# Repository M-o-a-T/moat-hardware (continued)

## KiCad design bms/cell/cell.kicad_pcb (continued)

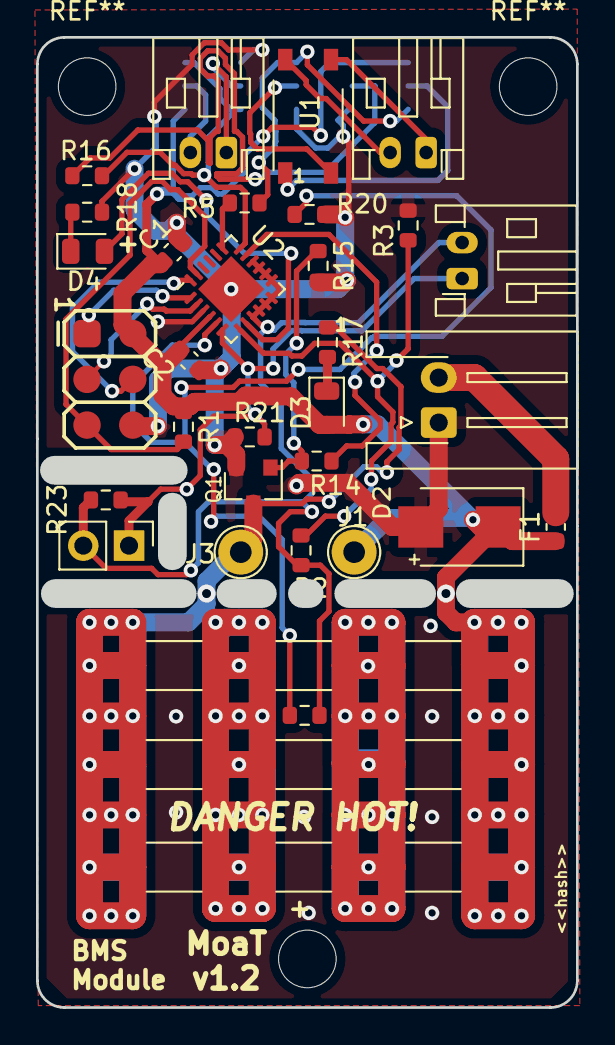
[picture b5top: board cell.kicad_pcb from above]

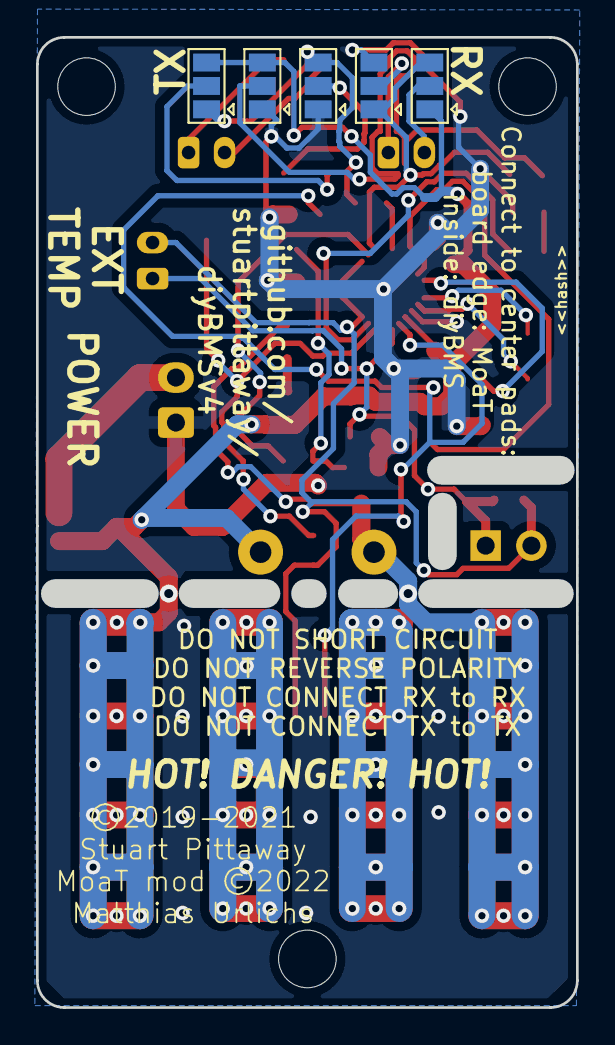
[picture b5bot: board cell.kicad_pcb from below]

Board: 2 copper layers, 30.0 x 53.9 mm, 44 parts (5 on the bottom side), 29 nets.

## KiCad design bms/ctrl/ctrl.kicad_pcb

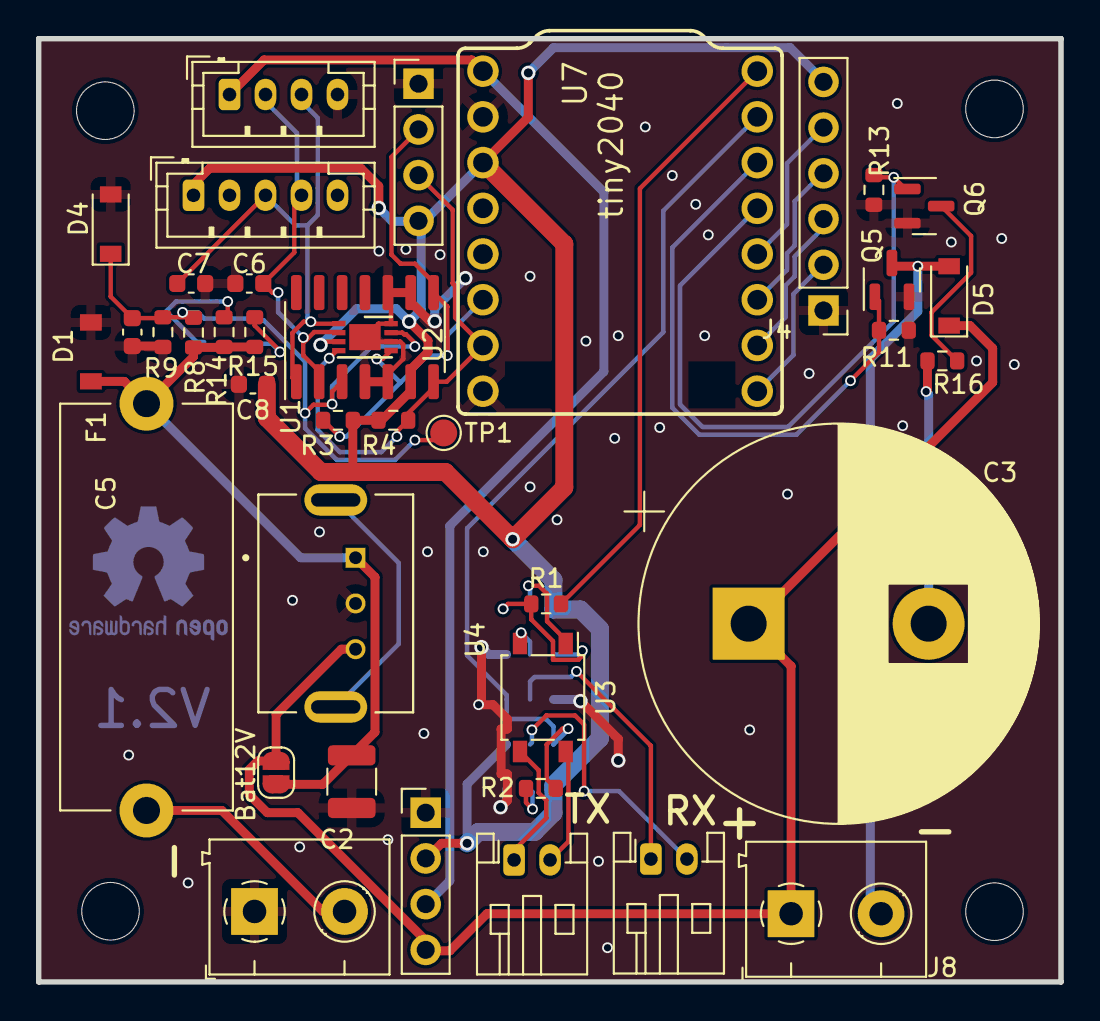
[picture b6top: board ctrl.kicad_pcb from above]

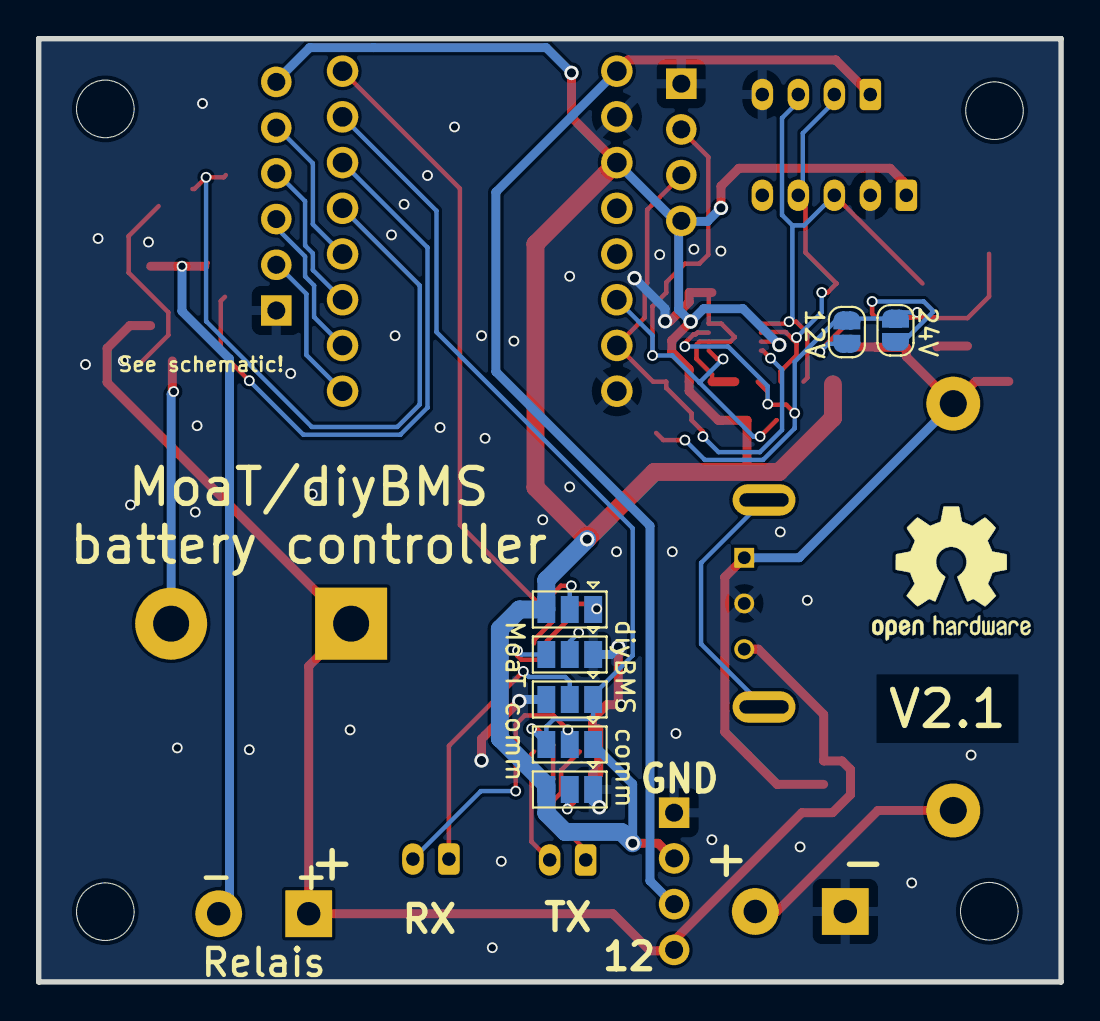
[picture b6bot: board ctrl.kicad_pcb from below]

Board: 2 copper layers, 56.8 x 52.4 mm, 46 parts (7 on the bottom side), 33 nets.

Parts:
C2: CP_1µ_100V_0805; R_1210_3225Metric
C3: CP_22m_16V; CP_Radial_D22.0mm_P10.00mm_SnapIn
C5, C6, C7, C8: CP_100n_50V_0603; C_0603_1608Metric
D1: D_TVS_70V; SOD-123FL
D4: D_Zener_3V3; D_SOD-123
D5: 1N4148; D_SOD-123
F1: Fuse; Fuseholder_Cylinder-5x20mm_Stelvio-Kontek_PTF78_Horizontal_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
J1, J8: Conn_01x02_Female; Conn_P5.0mm_2_Lumberg
J4: Conn_01x06; PinHeader_1x06_P2.54mm_Vertical
J5, J12: Conn_01x04; PinHeader_1x04_P2.54mm_Vertical
J6: Conn_LEM_5; JST_PH_B4B-PH-K_1x04_P2.00mm_Vertical
J10: Conn_LEM_3; JST_PH_B5B-PH-K_1x05_P2.00mm_Vertical
JP1, JP2, JP3, JP4, JP5: SolderJumper_3_Bridged12; SolderJumper-3_P1.3mm_Open_Pad1.0x1.5mm
JP11: Bat12V; SolderJumper-2_P1.3mm_Open_RoundedPad1.0x1.5mm
JP12: 24V; SolderJumper-2_P1.3mm_Open_RoundedPad1.0x1.5mm
JP13: 12V; SolderJumper-2_P1.3mm_Open_RoundedPad1.0x1.5mm
Q5, Q6: DMN2058U-7; SOT-23
R1: R_220_0603; R_0603_1608Metric
R2: R_2k2_0603; R_0603_1608Metric
R3, R4: R_5k1_0603; R_0603_1608Metric
R8, R14, R15: R_750k_0603; R_0603_1608Metric
R9: R_36k_0603_1; R_0603_1608Metric
R11, R13: R_1M_0603; R_0603_1608Metric
R16: R_22_0603; R_0603_1608Metric
RX1: Conn_01x02_Male; JST_PH_S2B-PH-K_1x02_P2.00mm_Horizontal
TP1: TestPoint; TestPoint_Pad_D1.5mm
TX1: Conn_01x02_Male; JST_PH_S2B-PH-K_1x02_P2.00mm_Horizontal
U1: MCP3428; SOIC-14_3.9x8.7mm_P1.27mm
U2: MCP3426-xMC; DFN-8-1EP_3x2mm_P0.5mm_EP1.75x1.45mm
U3: VOS618A; SO-4_4.4x4.3mm_P2.54mm
U4: TSR_1-48150WI
U7: tiny2040

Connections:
+3V3: C8.1, J4.6, J5.4, J10.1 (+), J12.2, JP1.3 (B), JP3.1 (A), JP5.3 (B), R3.1, R4.1, U1.6 (VDD), U2.3 (VDD), U7.3 (3V3)
+5V: J6.1 (+), J12.3, U7.1 (VBUS)
+12V: C3.1, D5.1 (K), J8.1, J12.4, JP11.2 (B), U4.3 (+VOUT)
ADC_BAT_I: C7.1, J6.3 (Out), J10.3 (Out), U1.1 (CH1+), U2.1 (CH1+)
ADC_BAT_U: C5.1, D4.1 (K), JP12.2 (B), JP13.2 (B), R8.2, R9.1, TP1.1, U1.3 (CH2+), U2.7 (CH2+)
ADC_REF_I: C6.1, J6.2 (Ref), J10.4 (Ref), U1.2 (CH1-), U2.2 (CH1-)
GND: C2.2, C5.2, C6.2, C7.2, C8.2, D1.2 (A), D4.2 (A), J1.1, J4.1, J5.1, J6.4 (GND), J10.2 (GND), J12.1, JP2.1 (A), JP4.3 (B), JP5.1 (A), Q5.2 (S), Q6.2 (S), R9.2, R11.2, R13.2, U1.4 (CH2-), U1.5 (VSS), U1.9 (Adr0), U1.10 (Adr1), U2.6 (VSS), U2.8 (CH2-), U2.9 (VSS), U4.2 (GND), U7.2 (GND), U7.8 (GND)
I2C0_SCL: J5.2, R3.2, U1.8 (SCL), U2.5 (SCL), U7.6 (GP27)
I2C0_SDA: J5.3, R4.2, U1.7 (SDA), U2.4 (SDA), U7.7 (GP26)
IO1: J4.5, U7.12 (GP4)
IO2: J4.4, U7.11 (GP5)
IO3: J4.3, U7.10 (GP6)
IO4: J4.2, U7.9 (GP7)
unnamed: C3.2, R16.2
unnamed: D5.2 (A), J8.2, Q5.3 (D)
unnamed: F1.1, J1.2
unnamed: JP1.1 (A), JP2.3 (B), R1.1
unnamed: JP1.2 (C), U3.1
unnamed: JP2.2 (C), U3.2
unnamed: JP3.2 (C), RX1.2
unnamed: JP4.2 (C), RX1.1
unnamed: JP5.2 (C), R2.2
unnamed: JP12.1 (A), R14.2
unnamed: JP13.1 (A), R15.2
unnamed: Q6.3 (D), R16.1
unnamed: TX1.1, U3.3
unnamed: TX1.2, U3.4
unnamed: U4.4 (CASE_PIN), U4.5 (CASE_PIN)
RELAY1: Q5.1 (G), R11.1, U7.14 (GP2)
RELAY2: Q6.1 (G), R13.1, U7.13 (GP3)
RX_BAT: JP3.3 (B), JP4.1 (A), R2.1, U7.15 (GP1)
TX_BAT: R1.2, U7.16 (GP0)
VBAT: C2.1, D1.1 (K), F1.2, JP11.1 (A), R8.1, R14.1, R15.1, U4.1 (+VIN)

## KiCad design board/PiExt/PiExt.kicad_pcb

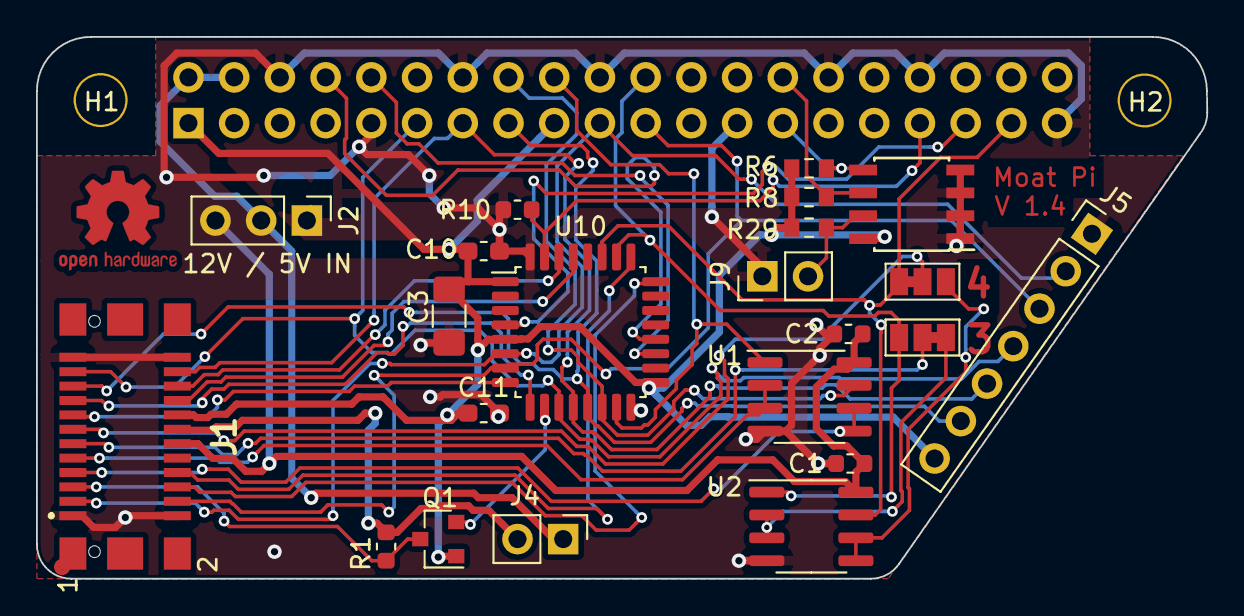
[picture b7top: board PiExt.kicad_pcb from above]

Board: 2 copper layers, 65.0 x 30.1 mm, 25 parts (1 on the bottom side), 36 nets.

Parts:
C1, C2: 100n; C_0603_1608Metric
C3: 10µF; C_1206_3216Metric_Pad1.42x1.75mm_HandSolder
C10, C11: 100nF; C_0603_1608Metric_Pad1.05x0.95mm_HandSolder
H1, H2: 3mm_Mounting_Hole; NPTH_3mm_ID
J1: Moat_Bus_device; TE_1775013_plug
J2: CONN_01X03; PinHeader_1x03_P2.54mm_Vertical
J3: 40HAT; PinSocket_2x20_P2.54mm_Vertical
J4, J9: CONN_01X02; PinHeader_1x02_P2.54mm_Vertical
J5: Conn_01x07; PinHeader_1x07_P2.54mm_Vertical
JP1, JP2: SolderJumper_3_Bridged12; SolderJumper-3_P1.3mm_Bridged12_Pad1.0x1.5mm_NumberLabels
Q1: 2N7002; SOT-23
R1: 10k; R_0603_1608Metric
R6, R8: 3.9K; R_0603_1608Metric_Pad0.84x1.00mm_HandSolder
R10: 100k; R_0603_1608Metric
R29: 1K; R_0603_1608Metric_Pad0.84x1.00mm_HandSolder
U1, U2: P82B96; SOIC-8_3.9x4.9mm_P1.27mm
U10: STM32L051K8Tx; LQFP-32_7x7mm_P0.8mm
U11: CAT24C32; SOIC-8_3.9x4.9mm_P1.27mm

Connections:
+3V3: C3.1, C10.1, C11.1, J1.16, J3.1, J3.17, J5.7, Q1.1, R6.1, R8.1, R29.1, U10.1, U10.5, U10.17, U11.8
+5V: J2.2, J3.2, J3.4, J4.1
+12V: C1.1, C2.1, J1.12, J2.3, U1.8, U2.8
/1wire: Q1.2, U10.10
/5v: J1.14, J4.2, R1.1
/Boot0: J3.33, R10.1, U10.31
/Bus1: J3.16, U1.7, U10.14
/Bus2: J3.18, U1.1, U10.15
/Bus3: J3.22, JP1.3, U2.1, U10.26
/Bus4: J3.37, JP2.1, U2.7, U10.27
/Common bus interface/1wire_5: J1.5, Q1.3, R1.2
/Common bus interface/Bus1_12: J1.7, U1.5, U1.6
/Common bus interface/Bus2_12: J1.9, U1.2, U1.3
/Common bus interface/Bus3_12: J1.11, JP1.2
/Common bus interface/Bus4_12: J1.13, JP2.2
/EN: J3.35, U10.4
/ID_SC_EEPROM: J3.28, R8.2, U11.6
/ID_SD_EEPROM: J3.27, R6.2, U11.5
/Rx: J3.8, U10.20
/Rx2: J1.17, U10.9
/Rx3: J1.8, U10.25
/SCLx: J1.18, U10.29
/SDAx: J1.20, U10.30
/SW1: J1.3, J3.19, J5.2, U10.6
/SW2: J1.4, J3.21, J5.3, U10.7
/T1: J1.21, J3.11, J5.4, U10.11
/T2: J1.22, J3.13, J5.5, U10.12
/T3: J1.19, J3.15, J5.6, U10.13
/Tx: J3.10, U10.19
/Tx2: J1.15, U10.8
/Tx3: J1.6, U10.24
GND: C1.2, C2.2, C3.2, C10.2, C11.2, J1.1, J1.2, J2.1, J3.6, J3.9, J3.14, J3.20, J3.25, J3.30, J3.34, J3.39, J5.1, J9.1, R10.2, U1.4, U2.4, U10.16, U10.32, U11.1, U11.2, U11.3, U11.4
GNDPWR: J1.23, J1.24
unnamed: J9.2, R29.2, U11.7
unnamed: JP1.1, U2.2, U2.3
unnamed: JP2.3, U2.5, U2.6
